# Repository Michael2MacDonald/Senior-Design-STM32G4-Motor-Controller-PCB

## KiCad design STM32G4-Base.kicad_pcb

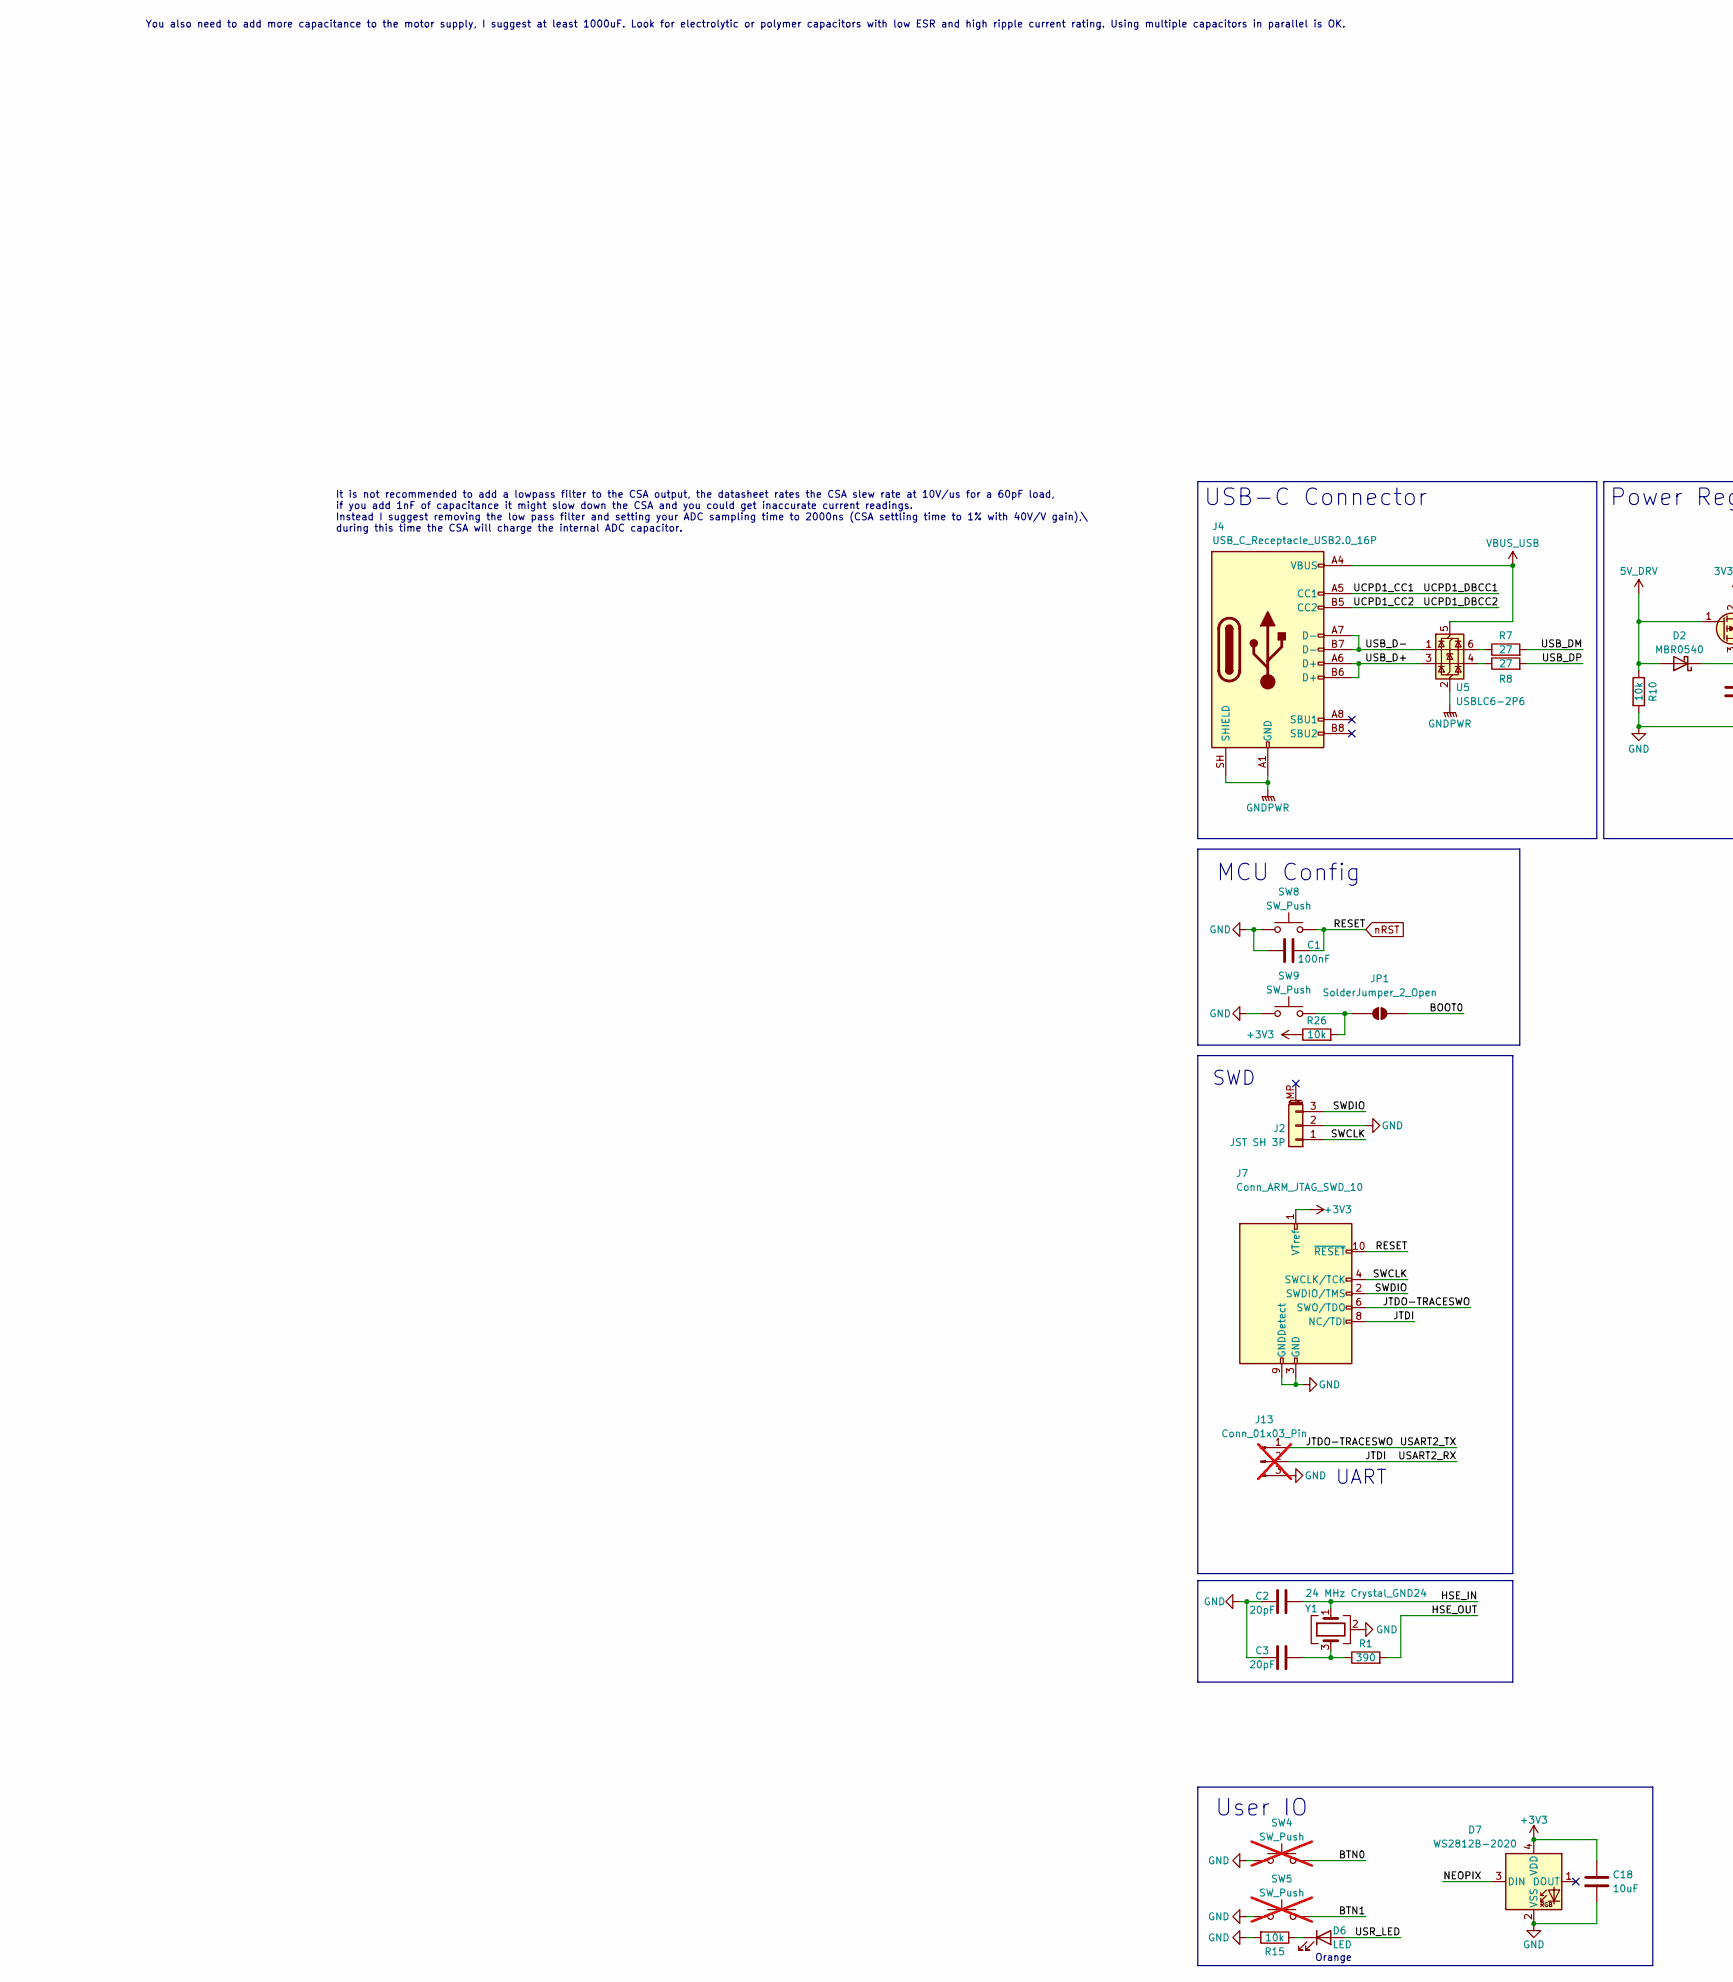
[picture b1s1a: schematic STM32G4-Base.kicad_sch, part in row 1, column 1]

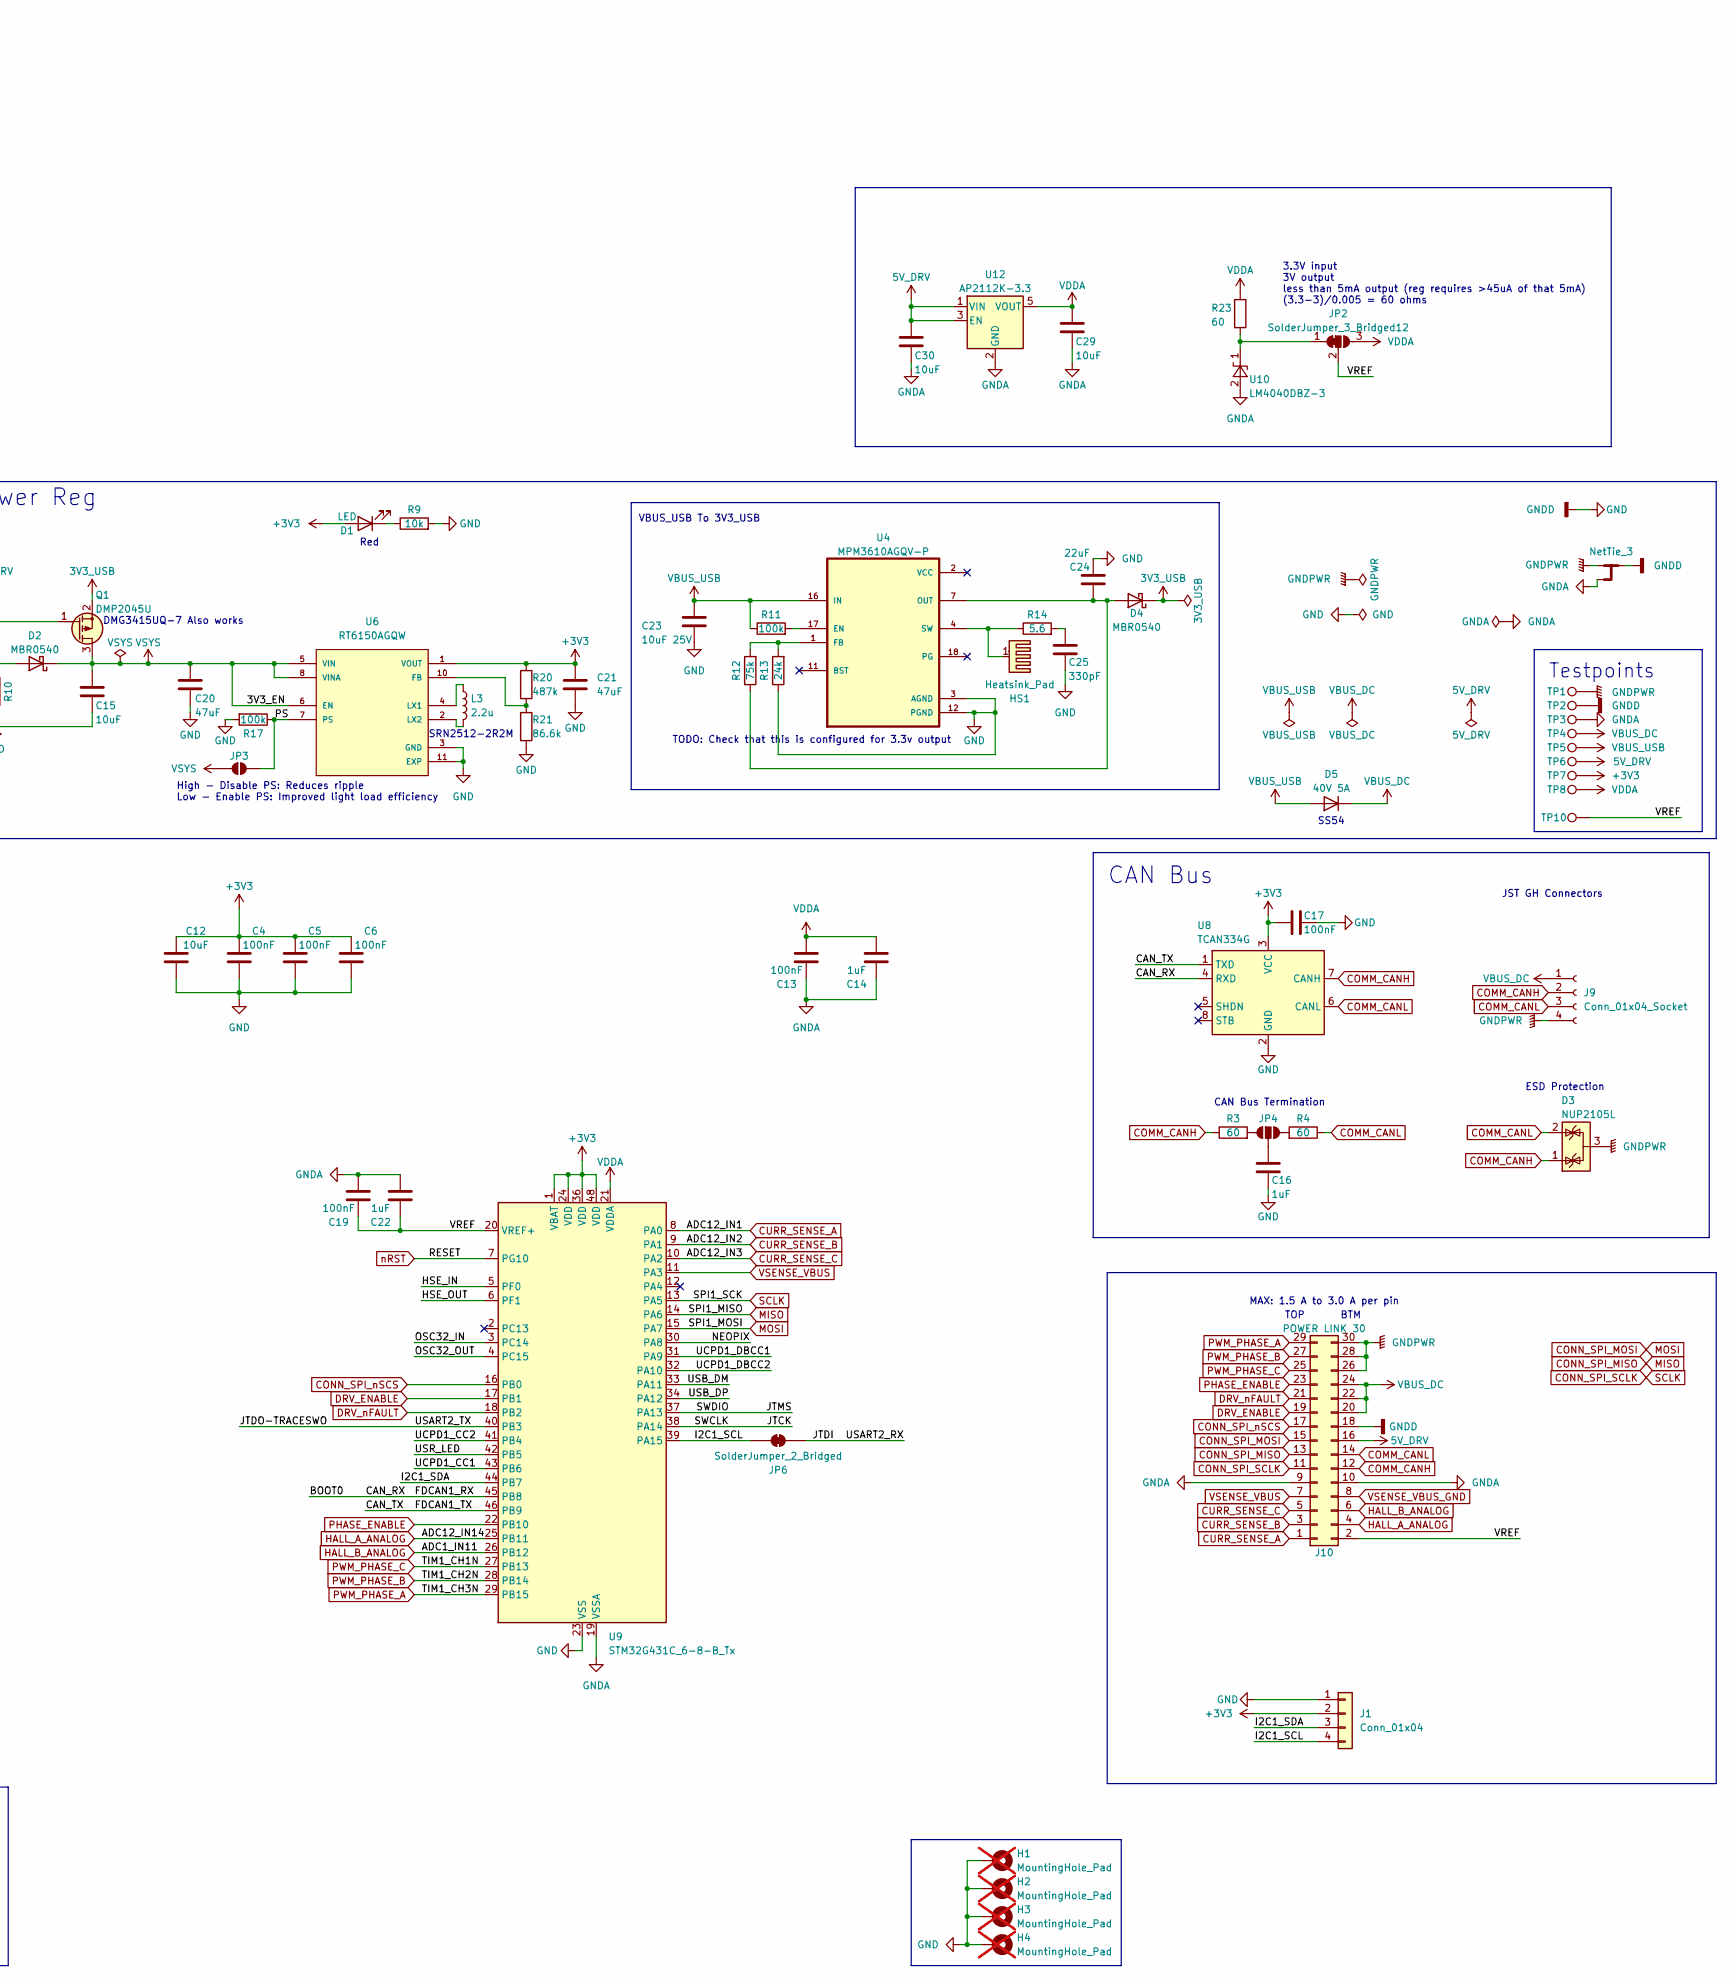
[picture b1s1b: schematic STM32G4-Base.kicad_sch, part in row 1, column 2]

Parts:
C1, C4, C5, C6, C13, C17, C19: 100nF; C_0402_1005Metric
C2, C3: 20pF; C_0603_1608Metric
C12: 10uF; C_0603_1608Metric
C14, C16, C22: 1uF; C_0603_1608Metric
C15, C18, C29, C30: 10uF; C_0603_1608Metric; LCSC Part Number C3015157
C20, C21: 47uF; C_0805_2012Metric; LCSC Part Number C16780
C23: 10uF 25V; C_0603_1608Metric
C24: 22uF; C_0603_1608Metric
C25: 330pF; C_0603_1608Metric
D1: LED; LED_0805_2012Metric; LCSC Part Number C497949
D2: MBR0540; D_SOD-123; LCSC Part Number C116159
D3: NUP2105L; SOT-23
D4: MBR0540; D_SOD-123
D5: 40V 5A; D_SMA
D6: LED; LED_0805_2012Metric
D7: WS2812B-2020; LED_WS2812B-2020_PLCC4_2.0x2.0mm; LCSC Part Number C965555
H1, H2, H3, H4: MountingHole_Pad; MountingHole_3.2mm_M3_Pad; not fitted
HS1: Heatsink_Pad
J1: Conn_01x04; JST_SH_SM04B-SRSS-TB_1x04-1MP_P1.00mm_Horizontal
J2: JST SH 3P; JST_SH_BM03B-SRSS-TB_1x03-1MP_P1.00mm_Vertical; LCSC Part Number C495538
J4: USB_C_Receptacle_USB2.0_16P; USB_C_Receptacle_G-Switch_GT-USB-7010ASV; LCSC Part Number C165948
J7: Conn_ARM_JTAG_SWD_10; PinHeader_2x05_P1.27mm_Vertical_SMD
J9: Conn_01x04_Socket; JST_GH_SM04B-GHS-TB_1x04-1MP_P1.25mm_Horizontal
J10: POWER LINK 30; PinHeader_2x15_P2.54mm_EdgeMount; MPN 62703021621
J13: Conn_01x03_Pin; PinHeader_1x03_P2.54mm_Vertical; not fitted
JP1, JP3: SolderJumper_2_Open; SolderJumper-2_P1.3mm_Open_RoundedPad1.0x1.5mm
JP2: SolderJumper_3_Bridged12; SolderJumper-3_P1.3mm_Bridged12_RoundedPad1.0x1.5mm
JP4: Jumper_3_NO_NoSilk
JP6: SolderJumper_2_Bridged; SolderJumper-2_P1.3mm_Bridged_RoundedPad1.0x1.5mm
L3: 2.2u; L_1008_2520Metric_Pad1.43x2.20mm_HandSolder; Manufacturer Part Number SRN2512-2R2M; LCSC Part Number C2041574
NT4: NetTie_3; NetTie-3_SMD_Pad0.5mm
Q1: DMP2045U; SOT-23; LCSC Part Number C459541
R1: 390; R_0603_1608Metric
R3, R4, R23: 60; R_0603_1608Metric
R7, R8: 27; R_0402_1005Metric; LCSC Part Number C25156
R9, R10, R15: 10k; R_0603_1608Metric; LCSC Part Number C25804
R11: 100k; R_0603_1608Metric
R12: 75k; R_0603_1608Metric
R13: 24k; R_0603_1608Metric
R14: 5.6; R_0603_1608Metric
R17: 100k; R_0603_1608Metric; LCSC Part Number C25803
R20: 487k; R_0402_1005Metric_Pad0.72x0.64mm_HandSolder
R21: 86.6k; R_0402_1005Metric_Pad0.72x0.64mm_HandSolder
R26: 10k; R_0603_1608Metric
SW4, SW5: SW_Push; SW_SPST_TS-1088-xR020; LCSC Part Number C720477; not fitted
SW8, SW9: SW_Push; SW_SPST_TS-1088-xR020; LCSC Part Number C720477
TP1, TP2, TP3, TP4, TP5, TP6, TP7, TP8, TP10: TestPoint; TestPoint_Pad_1.5x1.5mm
U4: MPM3610AGQV-P; CONV_MPM3620AGQV-P; PARTREV 1.0
U5: USBLC6-2P6; SOT-666
U6: RT6150AGQW; SON50P300X300X80-11N; Manufacturer Part Number RT6150AGQW; LCSC Package WDFN-10-EP(3x3)
U8: TCAN334G; TSOT-23-8
U9: STM32G431C_6-8-B_Tx; LQFP-48_7x7mm_P0.5mm
U10: LM4040DBZ-3; SOT-23
U12: AP2112K-3.3; SOT-23-5
Y1: 24 MHz Crystal_GND24; Crystal_SMD_2520-4Pin_2.5x2.0mm

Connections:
3V3_USB: D4.1 (K), Q1.2 (S)
5V_DRV: C30.1, D2.2 (A), J10.16, Q1.1 (G), R10.1, TP6.1 (1_1), U12.1 (VIN), U12.3 (EN)
+3V3: C4.1, C5.1, C6.1, C12.1, C17.1, C18.1, C21.1, D1.2 (A), D7.4 (VDD), J1.2, J7.1 (VTref), R20.1, R26.1, TP7.1 (1_1), U6.1 (VOUT), U8.3 (VCC), U9.1 (VBAT), U9.24 (VDD), U9.36 (VDD), U9.48 (VDD)
/BOOT0: JP1.2 (B), U8.4 (RXD), U9.45 (PB8)
/CAN_TX: U8.1 (TXD), U9.46 (PB9)
/HSE_IN: C2.2, U9.5 (PF0), Y1.1
/HSE_OUT: R1.2, U9.6 (PF1)
/I2C1_SCL: J1.4, JP6.1 (A), U9.39 (PA15)
/I2C1_SDA: J1.3, U9.44 (PB7)
/JTCK: J2.1, J7.4 (SWCLK/TCK), U9.38 (PA14)
/JTDI: J7.8 (NC/TDI), J13.2, JP6.2 (B)
/JTDO-TRACESWO: J7.6 (SWO/TDO), J13.1, U9.40 (PB3)
/JTMS: J2.3, J7.2 (SWDIO/TMS), U9.37 (PA13)
/NEOPIX: D7.3 (DIN), U9.30 (PA8)
/OSC32_IN: U9.3 (PC14)
/OSC32_OUT: U9.4 (PC15)
/PS: JP3.2 (B), R17.1, U6.7 (PS)
/UCPD1_CC1: J4.A5 (CC1), U9.31 (PA9), U9.43 (PB6)
/UCPD1_CC2: J4.B5 (CC2), U9.32 (PA10), U9.41 (PB4)
/USB_D+: J4.A6 (D+), J4.B6 (D+), U5.3 (I/O2)
/USB_D-: J4.A7 (D-), J4.B7 (D-), U5.1 (I/O1)
/USB_DM: R7.2, U9.33 (PA11)
/USB_DP: R8.2, U9.34 (PA12)
/USR_LED: D6.2 (A), U9.42 (PB5)
/VREF: C19.1, C22.1, J10.2, JP2.2 (C), TP10.1 (1_1), U9.20 (VREF+)
COMM_CANH: D3.1 (K), J9.2, J10.12, R3.1, U8.7 (CANH)
COMM_CANL: D3.2 (K), J9.3, J10.14, R4.1, U8.6 (CANL)
CONN_SPI_MISO: J10.13, U9.14 (PA6)
CONN_SPI_MOSI: J10.15, U9.15 (PA7)
CONN_SPI_SCLK: J10.11, U9.13 (PA5)
CONN_SPI_nSCS: J10.17, U9.16 (PB0)
CURR_SENSE_A: J10.1, U9.8 (PA0)
CURR_SENSE_B: J10.3, U9.9 (PA1)
CURR_SENSE_C: J10.5, U9.10 (PA2)
DRV_ENABLE: J10.19, U9.17 (PB1)
DRV_nFAULT: J10.21, U9.18 (PB2)
GND: C1.1, C2.1, C3.1, C4.2, C5.2, C6.2, C12.2, C15.2, C16.2, C17.2, C18.2, C20.2, C21.2, C23.2, C24.2, C25.2, D7.2 (VSS), H1.1, H2.1, H3.1, H4.1, J1.1, J2.2, J7.3 (GND), J7.5 (GND), J7.9 (GNDDetect), J10.18, J13.3, NT4.2, R9.2, R10.2, R13.1, R15.2, R17.2, R21.2, SW4.1, SW5.1, SW8.1, SW9.1, TP2.1 (1_1), U4.3 (AGND), U4.12 (PGND), U4.13 (PGND), U4.14 (PGND), U6.3 (GND), U6.9 (GND), U6.11 (EXP), U8.2 (GND), U9.23 (VSS), U9.35 (VSS), U9.47 (VSS), Y1.2 (G), Y1.4 (G)
GNDA: C13.1, C14.1, C19.2, C22.2, C29.2, C30.2, J10.9, J10.10, NT4.3, TP3.1 (1_1), U9.19 (VSSA), U10.2 (A), U12.2 (GND)
GNDPWR: D3.3 (A), J4.A1 (GND), J4.A12 (GND), J4.B1 (GND), J4.B12 (GND), J4.SH (SHIELD), J9.4, J10.26, J10.28, J10.30, NT4.1, TP1.1 (1_1), U5.2 (GND)
HALL_A_ANALOG: J10.4, U9.25 (PB11)
HALL_B_ANALOG: J10.6, U9.26 (PB12)
unnamed: C3.2, R1.1, Y1.3
unnamed: C25.1, R14.2
unnamed: D1.1 (K), R9.1
unnamed: C24.1, D4.2 (A), R12.1, U4.7 (OUT), U4.8 (OUT), U4.9 (OUT), U4.20 (OUT)
unnamed: D6.1 (K), R15.1
unnamed: JP1.1 (A), R26.2, SW9.2
unnamed: JP2.1 (A), R23.2, U10.1 (K)
unnamed: JP4.1 (A), R3.2
unnamed: C16.1, JP4.2 (B)
unnamed: JP4.3 (C), R4.2
unnamed: R7.1, U5.6 (I/O1)
unnamed: R8.1, U5.4 (I/O2)
unnamed: HS1.1, R14.1, U4.4 (SW), U4.5 (SW), U4.6 (SW), U4.19 (SW)
unnamed: R11.2, U4.17 (EN)
unnamed: R12.2, R13.2, U4.1 (FB)
unnamed: R20.2, R21.1, U6.10 (FB)
unnamed: L3.1, U6.4 (LX1)
unnamed: L3.2, U6.2 (LX2)
PHASE_ENABLE: J10.23, U9.22 (PB10)
PWM_PHASE_A: J10.29, U9.29 (PB15)
PWM_PHASE_B: J10.27, U9.28 (PB14)
PWM_PHASE_C: J10.25, U9.27 (PB13)
VBUS_DC: D5.1 (K), J9.1, J10.20, J10.22, J10.24, TP4.1 (1_1)
VBUS_USB: C23.1, D5.2 (A), J4.A4 (VBUS), J4.A9 (VBUS), J4.B4 (VBUS), J4.B9 (VBUS), R11.1, TP5.1 (1_1), U4.16 (IN), U5.5 (VBUS)
VDDA: C13.2, C14.2, C29.1, JP2.3 (B), R23.1, TP8.1 (1_1), U9.21 (VDDA), U12.5 (VOUT)
VSENSE_VBUS: J10.7, U9.11 (PA3)
VSENSE_VBUS_GND: J10.8
VSYS: C15.1, C20.1, D2.1 (K), JP3.1 (A), Q1.3 (D), U6.5 (VIN), U6.6 (EN), U6.8 (VINA)
nRST: C1.2, J7.10 (~RESET), SW8.2, U9.7 (PG10)

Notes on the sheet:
JST GH Connectors
MCU Config
You also need to add more capacitance to the motor supply, I suggest at least 1000uF. Look for electrolytic or polymer capacitors with low ESR and high ripple current rating. Using multiple capacitors in parallel is OK.
TODO: Check that this is configured for 3.3v output
DMG3415UQ-7 Also works
User IO
Red
VBUS_USB To 3V3_USB
SS54
It is not recommended to add a lowpass filter to the CSA output, the datasheet rates the CSA slew rate at 10V/us for a 60pF load, if you add 1nF of capacitance it might slow down the CSA and you could get inaccurate current readings. Instead I suggest removing the low pass filter and setting your A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
Orange
USB-C Connector
3.3V input 3V output less than 5mA output (reg requires >45uA of that 5mA) (3.3-3)/0.005 = 60 ohms
UART
SRN2512-2R2M
CAN Bus Termination
SWD
CAN Bus
Power Reg
MAX: 1.5 A to 3.0 A per pin
ESD Protection
BTM
High - Disable PS: Reduces ripple Low - Enable PS: Improved light load efficiency
TOP
Testpoints

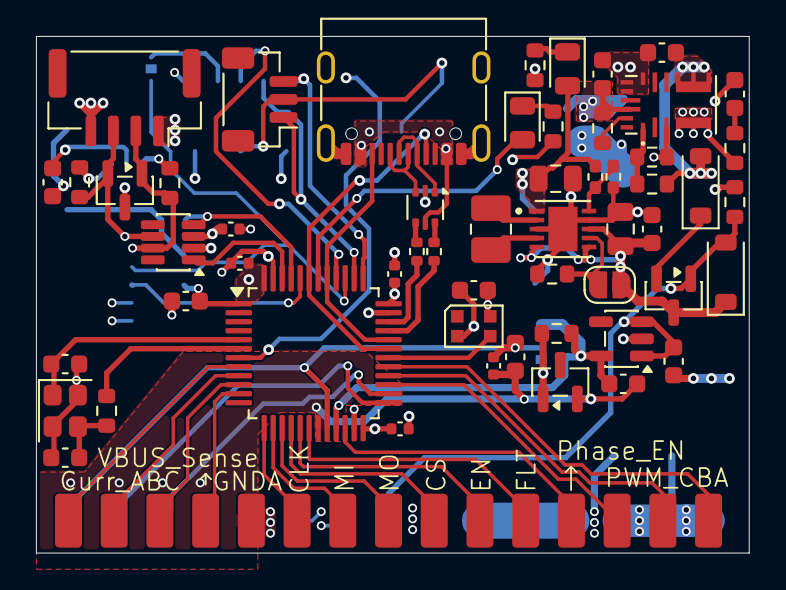
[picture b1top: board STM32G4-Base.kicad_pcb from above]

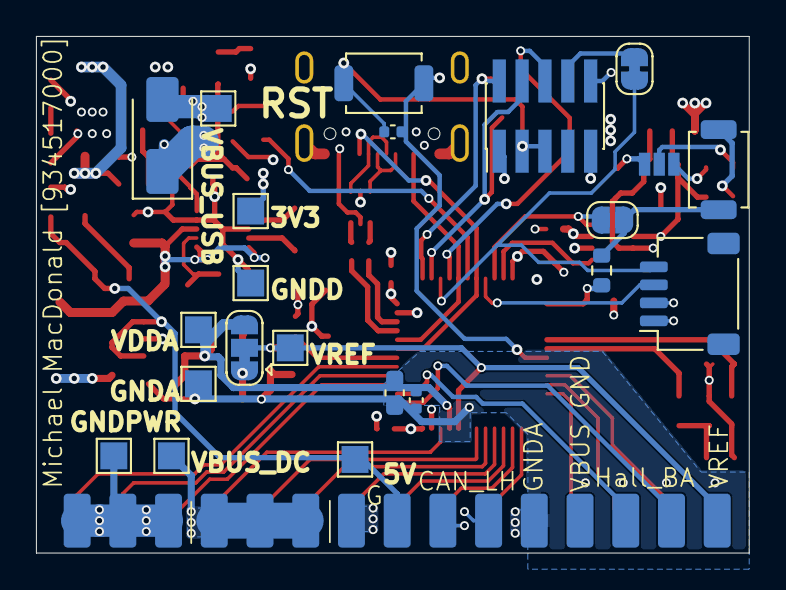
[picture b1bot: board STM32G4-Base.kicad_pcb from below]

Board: 4 copper layers, 39.6 x 28.7 mm, 79 parts (23 on the bottom side), 67 nets.
